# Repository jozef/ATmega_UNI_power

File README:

NAME

    ATmega UNI Power - 3.3V and 5V shield for ATmega UNI

DESCRIPTION

    Shield providing 3.3V and 5V to ATmega UNI.

SEE ALSO

    https://blog.kutej.net/2019/10/ATmega-UNI-Power,
    https://blog.kutej.net/2019/08/ATmega-UNI

LICENSE

    This is free software & hardware, licensed under the MIT License.

AUTHOR

        Jozef Kutej

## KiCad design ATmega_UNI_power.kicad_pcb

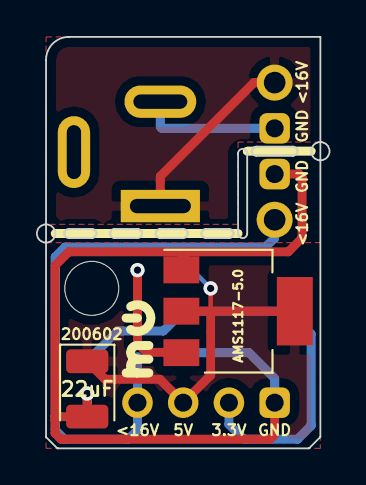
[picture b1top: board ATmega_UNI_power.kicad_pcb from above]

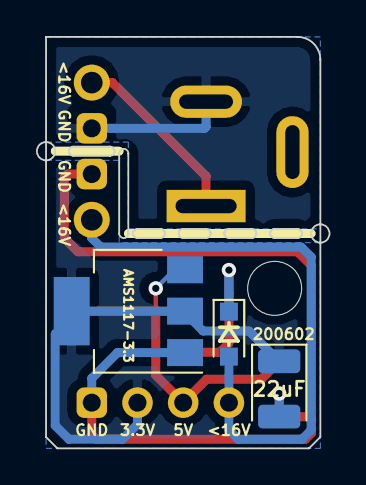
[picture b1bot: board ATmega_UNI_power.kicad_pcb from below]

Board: 2 copper layers, 16.3 x 22.9 mm, 9 parts (3 on the bottom side), 7 nets.

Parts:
C32, C52: 22uF; CP_EIA-3528-21_Kemet-B
D5: D; D_SOD-323_HandSoldering_F_SilkS_Sym
J1: Barrel_Jack_MountingPin; BarrelJack_Wuerth_6941xx301002_no_lines
J9: Power_Conn; PinSocket_1x04_P2.54mm_Vertical_no_lines
J91, J92: RAW_Conn; PinHeader_1x02_P2.54mm_Vertical_no_lines
U33: AMS1117-3.3; SOT-223-3_TabPin2
U55: AMS1117-5.0; SOT-223-3_TabPin2

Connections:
3.3V: C32.1, J9.2, U33.2
5V: C52.1, J9.3, U33.3, U55.2
GND: C32.2, C52.2, J9.1, J91.1, U33.1, U55.1
unnamed: J1.1, J92.2
unnamed: J1.2, J92.1
RAW: D5.1, U55.3
RAW_JACK: D5.2, J9.4, J91.2

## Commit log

2019-10-06 initial
2019-10-06 make it 600x900 mils
2019-10-22 remove power jack so it can go directly on a board below
2019-10-24 add jack back, but with break-away drills
2019-11-04 adjust break-out holes
2020-05-11 use ams1117 also for 3.3V, rm led power-on indication
2020-06-03 bigger raw bridge holes
